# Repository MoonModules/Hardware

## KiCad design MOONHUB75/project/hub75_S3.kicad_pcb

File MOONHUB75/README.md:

# MOONHUB75

This project is a passive adapter board to connect a [Lilygo T7-S3](https://lilygo.cc/products/t7-s3) to a HUB75 Panel. 

## Connections

### HUB75
It features two Methods to connect the HUB75 Panel
|Mode|Description|
|----|-----------|
|1|Female Sockets to directly Plug onto the Panel|
|2|Male Pins, to use a 16-Pin Ribbon Cable|

This is heavily inspired by the [ESP-HUB75-Driver by rorosaurus](https://github.com/rorosaurus/esp32-hub75-driver/). There are also pictures visible there.

|Hub75|GPIO|
|--|--|
|R0|IO1|
|G0|IO5|
|B0|IO6|
|R1|IO7|
|LAT|IO8|
|B1|IO9|
|G1|IO13|
|A|IO16|
|B|IO48|
|C|IO47|
|D|IO21|
|E|IO38|
|CLK|IO18|
|OE|IO4|

### Audio
The board has multiple Audio connections, that are mapped to the same Pins. 

There is a Connection to directly connect the INMP441 circle PCBs to it and there is a single row to either connect different boards. We noticed that there are two different pinouts so there are solder bridges to swap some pins around. L/R is connected to ground

|I2S|GPIO|
|--|--|
|DA|IO10|
|CK|IO11|
|WS|IO12|

### JTAG

For Debug purposes the JTAG connection of the ESP are compacted into one connector
The pinout is made to match the JTAG connector of the [ESP-Prog](https://docs.espressif.com/projects/esp-iot-solution/en/latest/hw-reference/ESP-Prog_guide.html). 

## Schematic

An example schematic is included in the `schematics` folder.

## Production Files

All files needed for production (Gerber, BOM, CPL) are included in the `production` folder.

## Project Files

This project was developed in KICad. Those project files are in the `project` folder.

## License

This project is licensed under the CERN-OHL-S V2 License. For more information, see the `LICENSE` file in the root folder of the repository

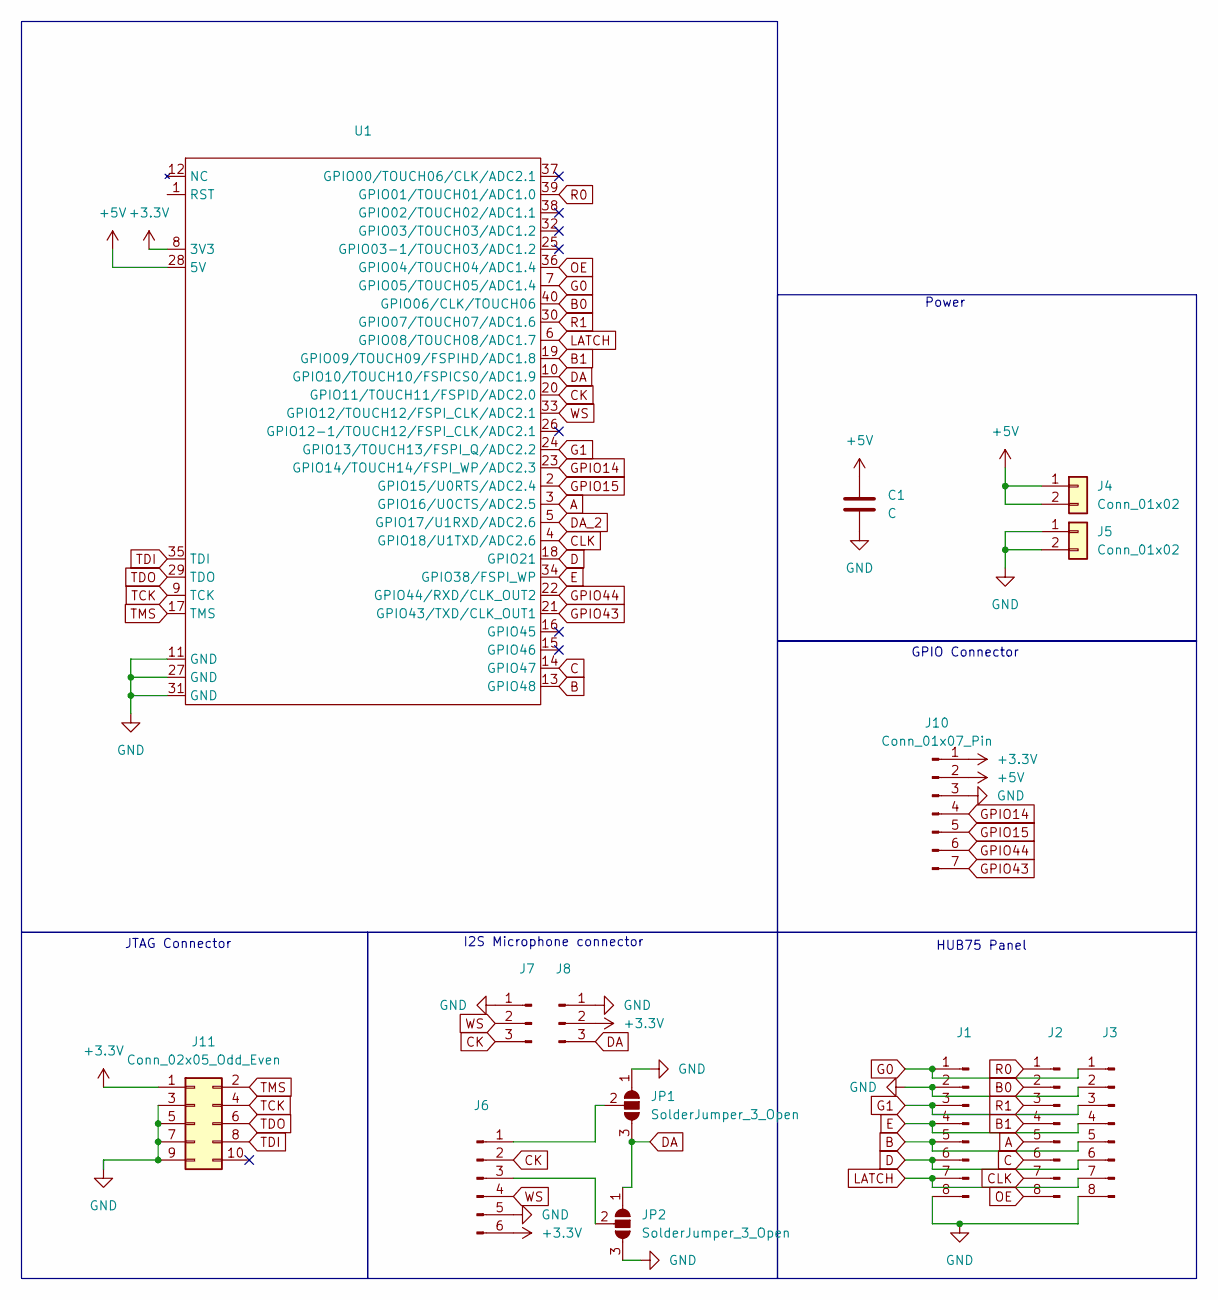
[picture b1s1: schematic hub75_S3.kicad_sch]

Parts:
C1: C; C_Radial_D10.0mm_H12.5mm_P5.00mm
J1, J2, J3: Conn_01x08_Pin; PinHeader_1x08_P2.54mm_Vertical
J4, J5: Conn_01x02; PhoenixContact_MSTBVA_2,5_2-G-5,08_1x02_P5.08mm_Vertical
J6: Conn_01x06_Pin; PinHeader_1x06_P2.54mm_Vertical
J7, J8: Conn_01x03_Pin; PinHeader_1x03_P2.54mm_Vertical
J10: Conn_01x07_Pin; PinHeader_1x07_P2.54mm_Vertical
J11: Conn_02x05_Odd_Even; PinHeader_2x05_P1.27mm_Vertical
JP1, JP2: SolderJumper_3_Open; SolderJumper-3_P1.3mm_Open_Pad1.0x1.5mm
U1: Lillygo T7-S3

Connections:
+3.3V: J6.6, J8.2, J10.1, J11.1, U1.8 (3V3)
+5V: C1.1, J4.1, J4.2, J10.2, U1.28 (5V)
A: J2.5, U1.3 (GPIO16/U0CTS/ADC2.5)
B: J1.5, J3.5, U1.13 (GPIO48)
B0: J2.2, U1.40 (GPIO06/CLK/TOUCH06)
B1: J2.4, U1.19 (GPIO09/TOUCH09/FSPIHD/ADC1.8)
C: J2.6, U1.14 (GPIO47)
CK: J6.2, J7.3, U1.20 (GPIO11/TOUCH11/FSPID/ADC2.0)
CLK: J2.7, U1.4 (GPIO18/U1TXD/ADC2.6)
D: J1.6, J3.6, U1.18 (GPIO21)
DA: J8.3, JP1.3 (B), JP2.1 (A), U1.10 (GPIO10/TOUCH10/FSPICS0/ADC1.9)
DA_2: U1.5 (GPIO17/U1RXD/ADC2.6)
E: J1.4, J3.4, U1.34 (GPIO38/FSPI_WP)
G0: J1.1, J3.1, U1.7 (GPIO05/TOUCH05/ADC1.4)
G1: J1.3, J3.3, U1.24 (GPIO13/TOUCH13/FSPI_Q/ADC2.2)
GND: C1.2, J1.2, J1.8, J3.2, J3.8, J5.1, J5.2, J6.5, J7.1, J8.1, J10.3, J11.3, J11.5, J11.7, J11.9, JP1.1 (A), JP2.3 (B), U1.11 (GND), U1.27 (GND), U1.31 (GND)
GPIO14: J10.4, U1.23 (GPIO14/TOUCH14/FSPI_WP/ADC2.3)
GPIO15: J10.5, U1.2 (GPIO15/U0RTS/ADC2.4)
GPIO43: J10.7, U1.21 (GPIO43/TXD/CLK_OUT1)
GPIO44: J10.6, U1.22 (GPIO44/RXD/CLK_OUT2)
LATCH: J1.7, J3.7, U1.6 (GPIO08/TOUCH08/ADC1.7)
unnamed: J6.1, JP1.2 (C)
unnamed: J6.3, JP2.2 (C)
OE: J2.8, U1.36 (GPIO04/TOUCH04/ADC1.4)
R0: J2.1, U1.39 (GPIO01/TOUCH01/ADC1.0)
R1: J2.3, U1.30 (GPIO07/TOUCH07/ADC1.6)
TCK: J11.4, U1.9 (TCK)
TDI: J11.8, U1.35 (TDI)
TDO: J11.6, U1.29 (TDO)
TMS: J11.2, U1.17 (TMS)
WS: J6.4, J7.2, U1.33 (GPIO12/TOUCH12/FSPI_CLK/ADC2.1)

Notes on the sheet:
HUB75 Panel
Power
GPIO Connector
JTAG Connector
I2S Microphone connector

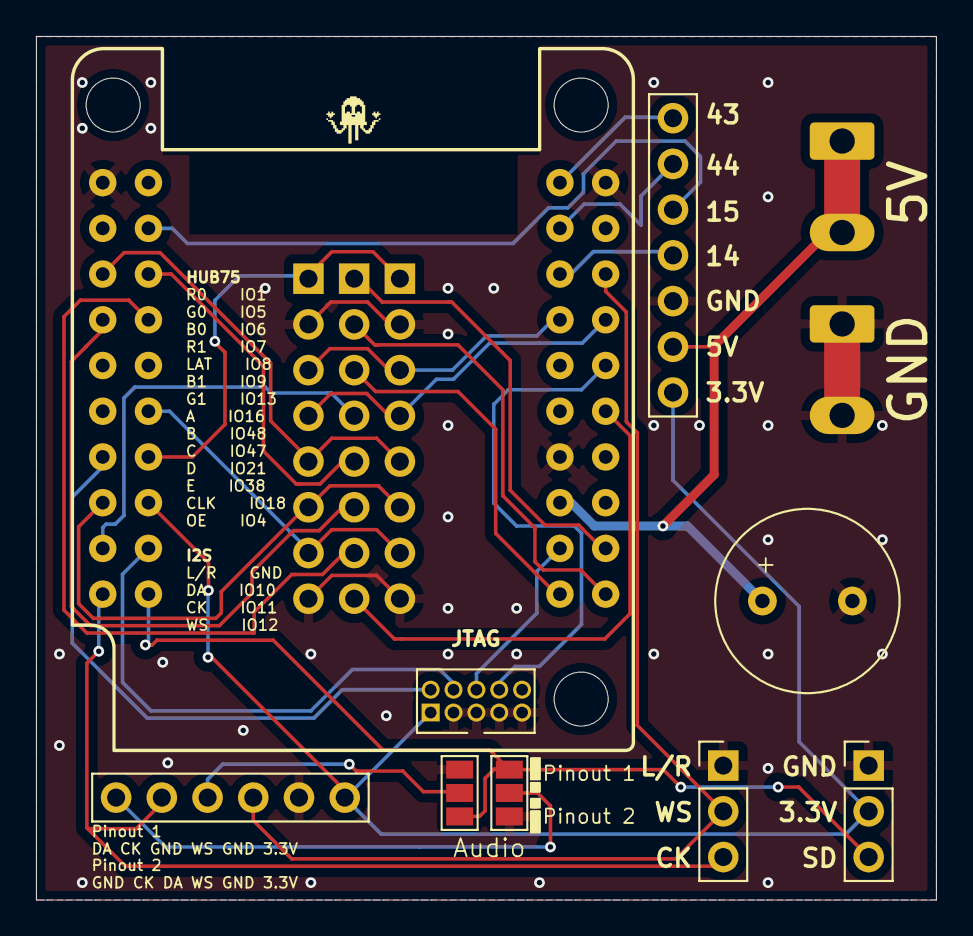
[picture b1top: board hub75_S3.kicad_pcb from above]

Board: 2 copper layers, 50.0 x 48.0 mm, 14 parts (0 on the bottom side), 30 nets.

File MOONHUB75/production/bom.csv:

Designator,Footprint,Quantity,Value,LCSC Part #
C1,C_Radial_D10.0mm_H12.5mm_P5.00mm,1,C,
"J1, J2, J3",PinHeader_1x08_P2.54mm_Vertical,3,Conn_01x08_Pin,
J10,PinHeader_1x07_P2.54mm_Vertical,1,Conn_01x07_Pin,
J11,PinHeader_2x05_P1.27mm_Vertical,1,Conn_02x05_Odd_Even,
"J4, J5","PhoenixContact_MSTBVA_2,5_2-G-5,08_1x02_P5.08mm_Vertical",2,Conn_01x02,
J6,PinHeader_1x06_P2.54mm_Vertical,1,Conn_01x06_Pin,
"J7, J8",PinHeader_1x03_P2.54mm_Vertical,2,Conn_01x03_Pin,
U1,Lillygo T7-S3,1,~,

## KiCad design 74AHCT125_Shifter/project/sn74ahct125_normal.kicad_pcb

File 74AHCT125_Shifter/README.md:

# SN74AHCT125 shifter breakout PCB

This project describes a breakout board for the 74AHCT125 Quad Buffer/Line Driver IC, used as a level shifter. The 74AHCT125 can shift signals from a lower voltage level, such as 3.3V, to a higher level, such as 5V. This is particularly useful when connecting microcontrollers with different voltage levels.
It's intended use is to shift the LED data line from an ESP to drive digital LEDs like the WS2812b, but it can be used for a lot of different usecases.

## Overview

The 74AHCT125 consists of four independent buffer/line driver units with three-state outputs and active-low enable (OE) inputs. The OE inputs allow each of the four channels to be controlled individually. The chip operates with a supply voltage of 4.5 to 5.5V and can shift signals to a 5V level when powered at 5V.

This breakout board provides an easy way to use the 74AHCT125 in level-shifting applications. With its modular design, the board can be used for both single-channel and multi-channel applications.

## Features

- **IC**: 74AHCT125 Quad Buffer/Line Driver with three-state outputs
- **Voltage Level**: Converts 3.3V signals to 5V
- **Four Independent Channels**: Each channel can be enabled separately
- **Simple Breakout Design**: Access to all pins of the IC
- **Operating Voltage**: 4.5V to 5.5V (typically 5V)

## Pinout

| IC Pin | Description                  |
|--------|------------------------------|
| VCC    | Supply voltage (5V)          |
| GND    | Ground                       |
| I1-I4  | Inputs of channels 1 to 4    |
| O1-O4  | Outputs of channels 1 to 4   |

## Usage Example

1. Connect the VCC pin to 5V and the GND pin to ground.
2. Connect a data output from a microcontroller to the A input of any channel.
3. The corresponding Y output will provide a 5V data signal, which can be safely used with 5V logic devices.
4. To enable a channel, set the corresponding solderjumpers on the bottom of the PCB.
## Notes

- The 74AHCT125 is designed for one-way level-shifting, typically from 3.3V to 5V. It is not suitable for bidirectional level-shifting.
- Ensure the OE pin for each active channel is set to low to enable the output.
- if a channel is unused, please disable that channel with the solder jumpers on the bottom.

## Schematic

An example schematic is included in the `schematics` folder.

## Production Files

All files needed for production (Gerber, BOM, CPL) are included in the `production` folder.

## Project Files

This project was developed in KICad. Those project files are in the `project` folder.

## License

This project is licensed under the CERN-OHL-S V2 License. For more information, see the `LICENSE` file in the root folder of the repository

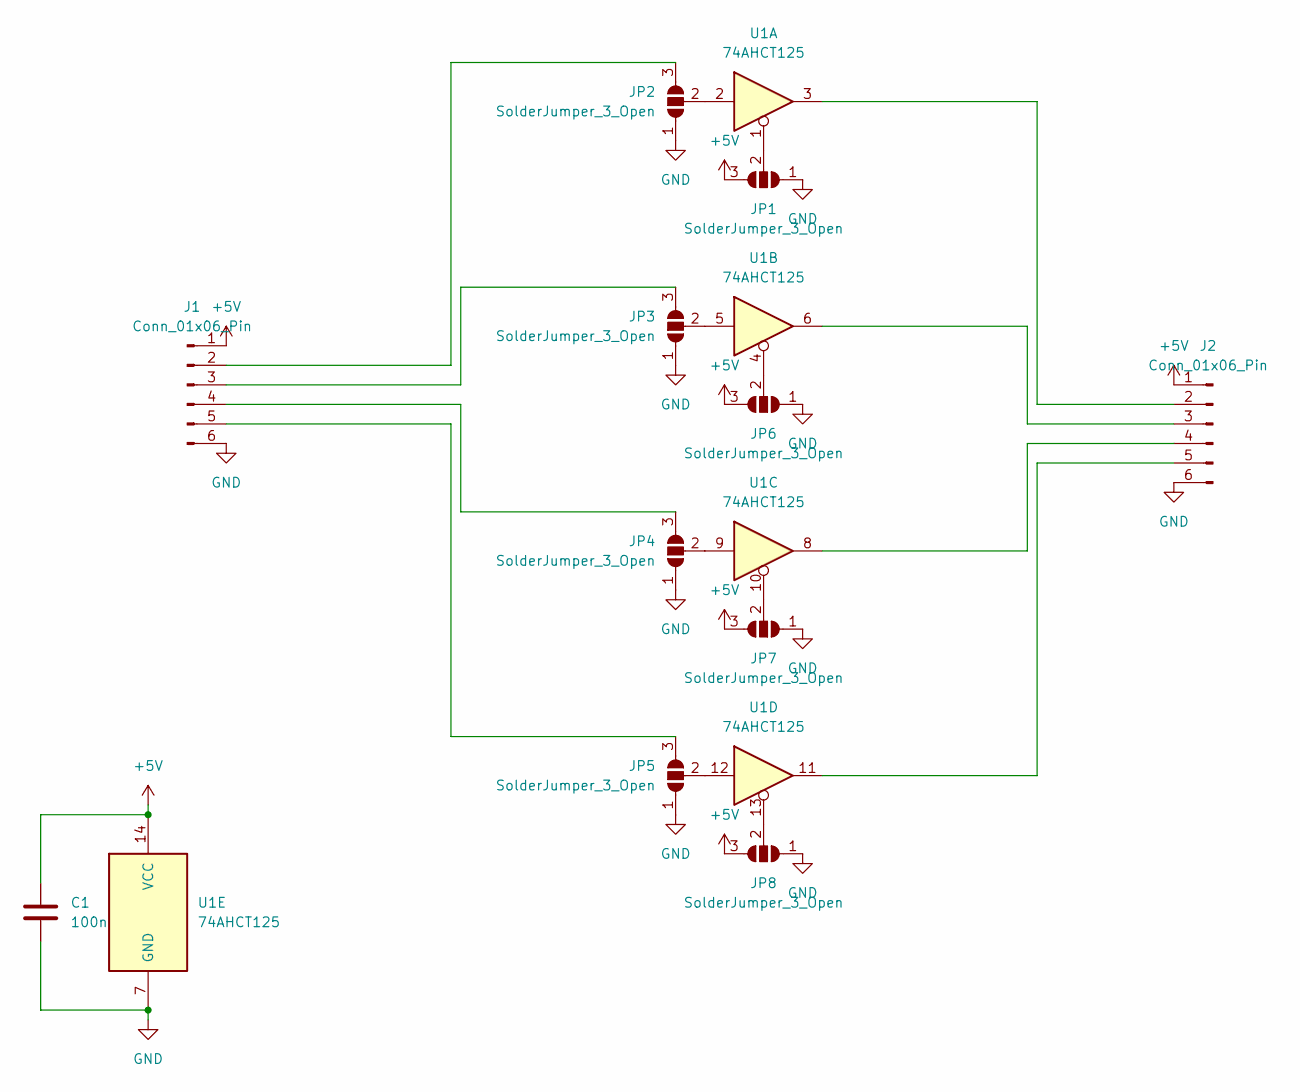
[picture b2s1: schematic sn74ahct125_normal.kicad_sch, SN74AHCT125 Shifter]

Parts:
C1: 100n; C_1206_3216Metric_Pad1.33x1.80mm_HandSolder
J1, J2: Conn_01x06_Pin; PinHeader_1x06_P2.54mm_Vertical
JP1, JP2, JP3, JP4, JP5, JP6, JP7, JP8: SolderJumper_3_Open; SolderJumper-3_P1.3mm_Open_Pad1.0x1.5mm_NumberLabels
U1: 74AHCT125; SOIC-14_3.9x8.7mm_P1.27mm

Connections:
+5V: C1.1, J1.1, J2.1, JP1.3 (B), JP6.3 (B), JP7.3 (B), JP8.3 (B), U1.14 (VCC)
GND: C1.2, J1.6, J2.6, JP1.1 (A), JP2.1 (A), JP3.1 (A), JP4.1 (A), JP5.1 (A), JP6.1 (A), JP7.1 (A), JP8.1 (A), U1.7 (GND)
unnamed: J1.2, JP2.3 (B)
unnamed: J1.3, JP3.3 (B)
unnamed: J1.4, JP4.3 (B)
unnamed: J1.5, JP5.3 (B)
unnamed: J2.2, U1.3
unnamed: J2.3, U1.6
unnamed: J2.4, U1.8
unnamed: J2.5, U1.11
unnamed: JP1.2 (C), U1.1
unnamed: JP2.2 (C), U1.2
unnamed: JP3.2 (C), U1.5
unnamed: JP4.2 (C), U1.9
unnamed: JP5.2 (C), U1.12
unnamed: JP6.2 (C), U1.4
unnamed: JP7.2 (C), U1.10
unnamed: JP8.2 (C), U1.13

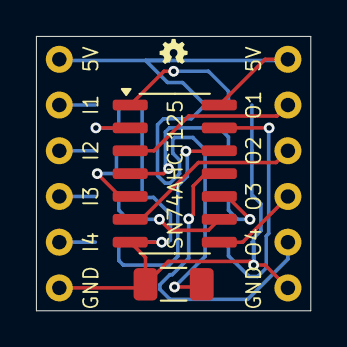
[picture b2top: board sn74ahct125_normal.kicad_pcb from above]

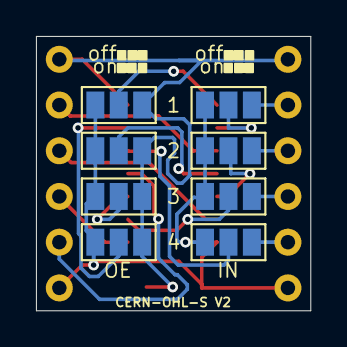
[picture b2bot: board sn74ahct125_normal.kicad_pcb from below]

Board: 2 copper layers, 15.2 x 15.2 mm, 12 parts (8 on the bottom side), 18 nets.

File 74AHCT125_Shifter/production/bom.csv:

Designator,Footprint,Quantity,Value,LCSC Part #
C1,1206,1,100n,
"J1, J2",PinHeader_1x06_P2.54mm_Vertical,2,Conn_01x06_Pin,
U1,SOIC-14_3.9x8.7mm_P1.27mm,1,74AHCT125,

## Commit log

2024-11-05 Create LICENSE
2024-11-07 Change License to CERN-OHL-S V2
    Changing to a Hardware license, since this repo will mostly contain hardware projects, and their files.
2024-11-09 Update README.md
    Add image
2025-01-06 Add Moonhub75
2025-01-11 Fixed Typo in Pinout
2025-09-13 Updated the PCB
    Moved the pinheader of the HUB Panel to line up in the grid of the T7S3.
    Added polarity marking on the capacitor
    Added 3mm mounting holes
2025-12-21 Adding Liliygo symbol and footprint
